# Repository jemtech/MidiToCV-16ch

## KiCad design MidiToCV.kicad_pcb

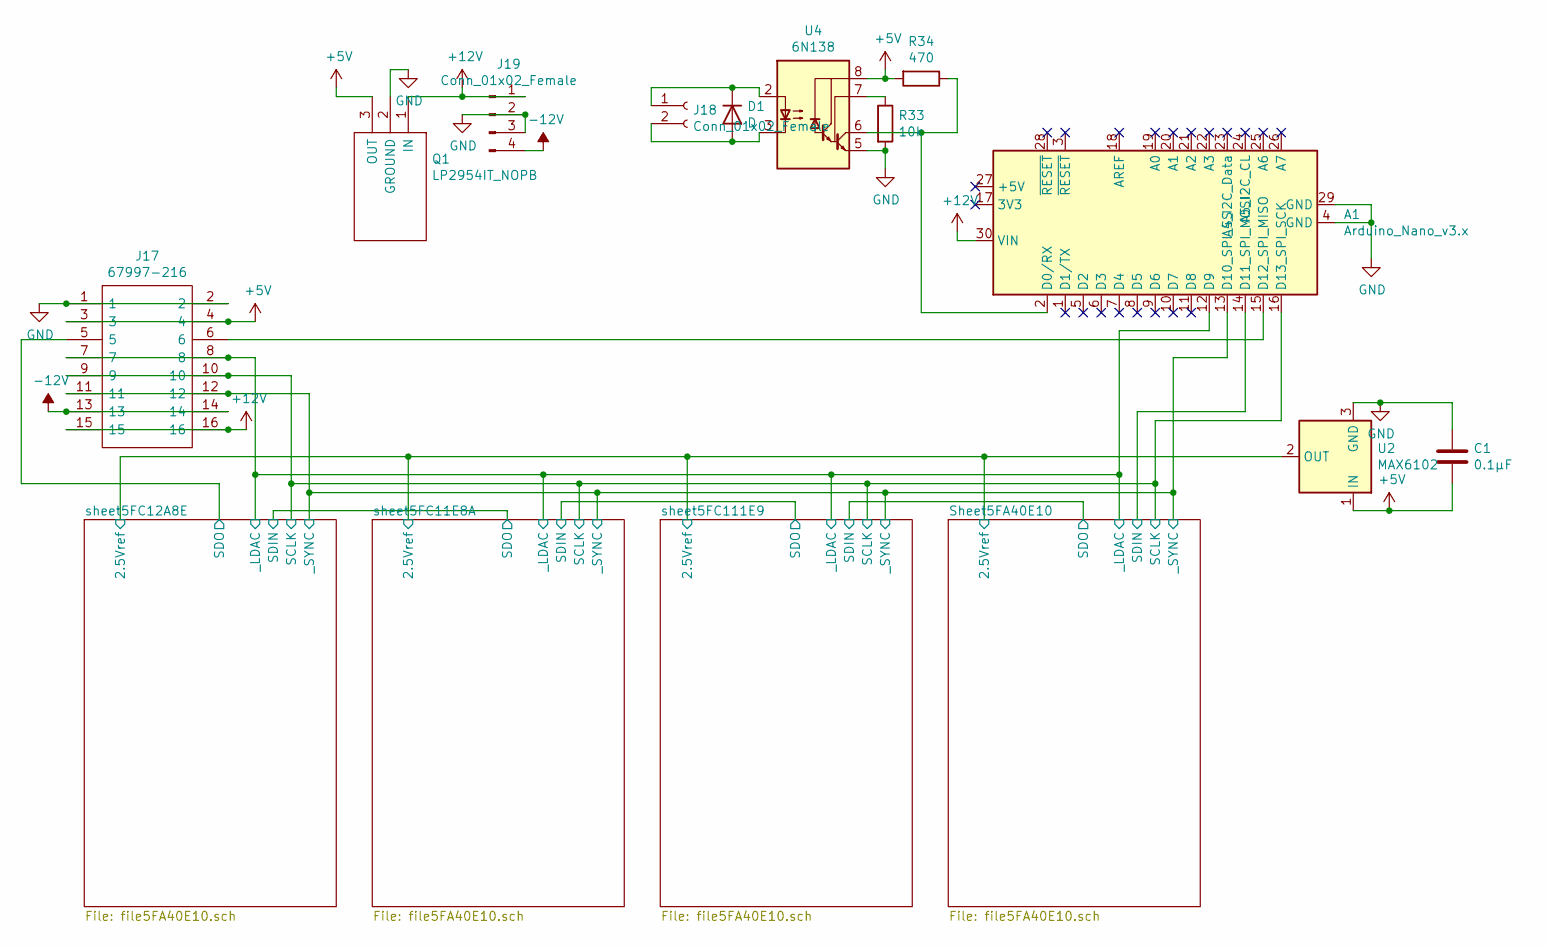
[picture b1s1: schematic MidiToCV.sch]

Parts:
A1: Arduino_Nano_v3.x; Arduino_Nano
C1: 0.1µF; C_0805_2012Metric_Pad1.15x1.40mm_HandSolder
D1: D; D_0805_2012Metric_Pad1.15x1.40mm_HandSolder
J17: 67997-216; HDRV16W90P254_2X8_2032X483X858P; Manufacturer_Part_Number 67997-216
J18: Conn_01x02_Female; PinHeader_1x02_P2.54mm_Vertical
J19: Conn_01x02_Female; PinHeader_1x04_P2.54mm_Vertical
Q1: LP2954IT_NOPB; TO254P470X1028X1955-3P; Mouser Part Number 926-LP2954IT/NOPB
R33: 10k; R_0805_2012Metric_Pad1.15x1.40mm_HandSolder
R34: 470; R_0805_2012Metric_Pad1.15x1.40mm_HandSolder
U2: MAX6102; SOT-23
U4: 6N138; SOP254P1016X460-8N

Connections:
+5V: C1.2, J17.3, J17.4, Q1.3 (OUT), R34.2, U2.1 (IN), U4.8 (VCC); also elsewhere on the board
+12V: A1.30 (VIN), J17.15, J17.16, J19.1, Q1.1 (IN); also elsewhere on the board
-12V: J17.13, J17.14, J19.4; also elsewhere on the board
/Sheet5FA40E10/2.5Vref: U2.2 (OUT); also elsewhere on the board
/Sheet5FA40E10/SCLK: A1.16 (D13_SPI_SCK), J17.9, J17.10; also elsewhere on the board
/Sheet5FA40E10/SDIN: A1.14 (D11_SPI_MOSI); also elsewhere on the board
/Sheet5FA40E10/_LDAC: A1.12 (D9), J17.7, J17.8; also elsewhere on the board
/Sheet5FA40E10/_SYNC: A1.13 (D10_SPI_SS), J17.11, J17.12; also elsewhere on the board
/sheet5FC12A8E/SDO: J17.5; also elsewhere on the board
GND: A1.4 (GND), A1.29 (GND), C1.1, J17.1, J17.2, J19.2, J19.3, Q1.2 (GROUND), R33.2, U2.3 (GND), U4.5 (GND); also elsewhere on the board
unnamed: A1.2 (D0/RX), R34.1, U4.6 (VO2)
unnamed: A1.15 (D12_SPI_MISO), J17.6
unnamed: D1.1 (K), J18.1, U4.2 (C1)
unnamed: D1.2 (A), J18.2, U4.3 (C2)
unnamed: R33.1, U4.7 (VO1)

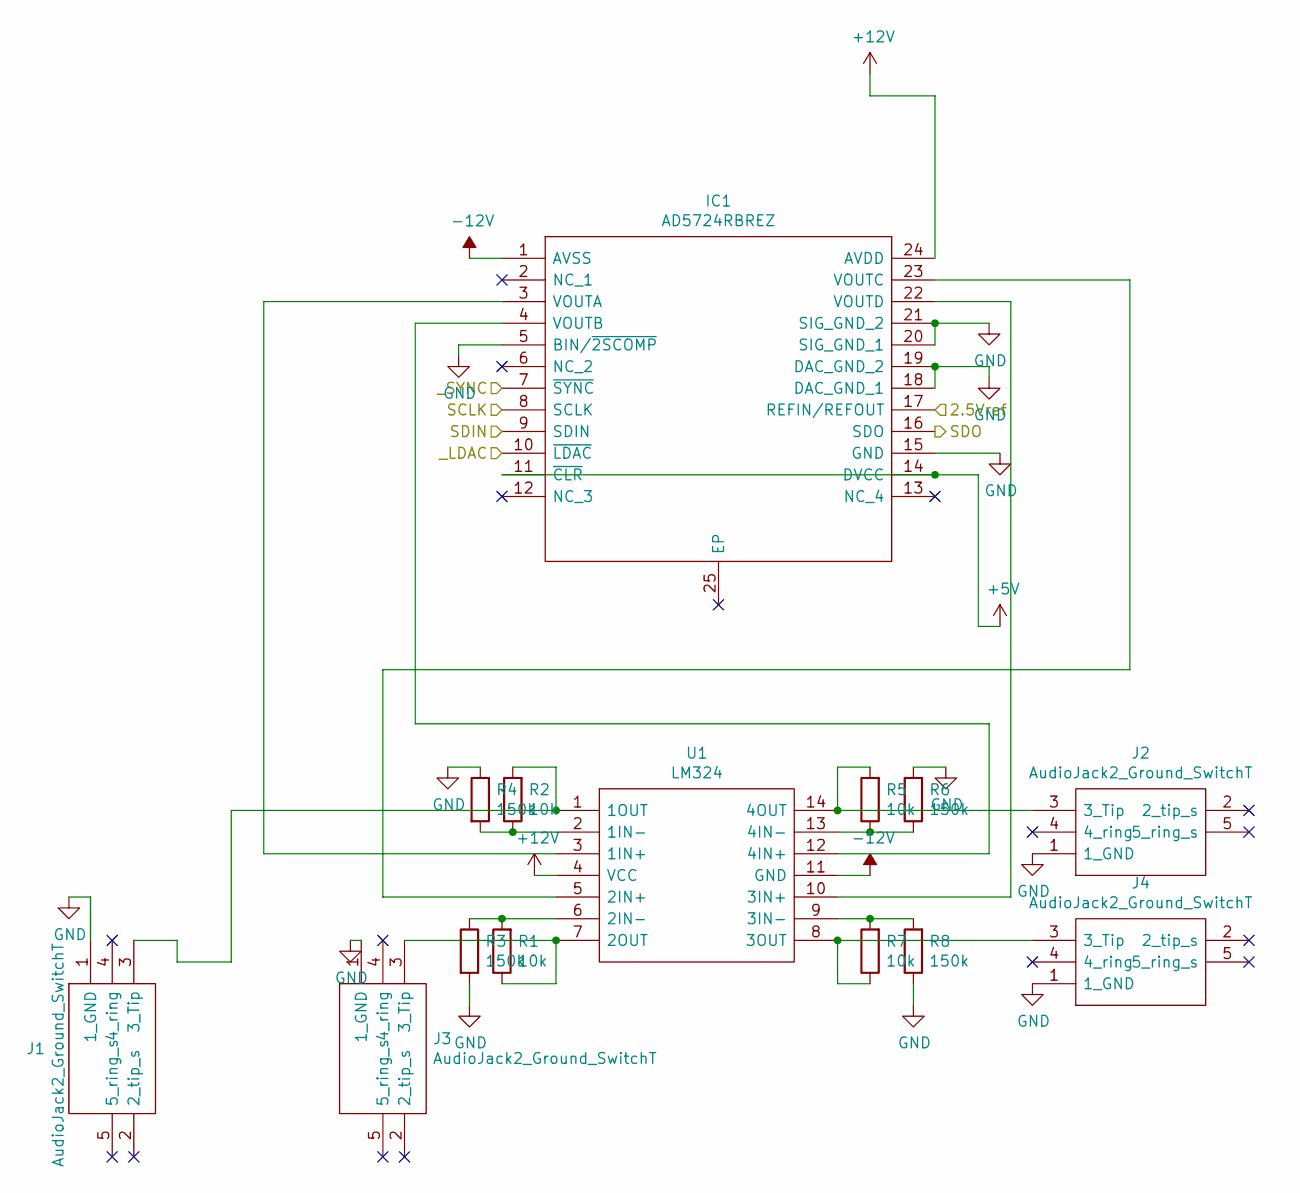
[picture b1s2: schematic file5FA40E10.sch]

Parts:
IC1: AD5724RBREZ; SOP65P640X120-25N; Mouser Part Number 584-AD5724RBREZ
J1, J2, J3, J4: AudioJack2_Ground_SwitchT; ACJS-NV35-XX; Manufacturer_Part_Number ACJS-NV35-5
R1, R2, R5, R7: 10k; R_0805_2012Metric_Pad1.15x1.40mm_HandSolder
R3, R4, R6, R8: 150k; R_0805_2012Metric_Pad1.15x1.40mm_HandSolder
U1: LM324; SOIC127P600X175-14N

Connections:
+5V: IC1.11 (~CLR), IC1.14 (DVCC); also elsewhere on the board
+12V: IC1.24 (AVDD), U1.4 (VCC); also elsewhere on the board
-12V: IC1.1 (AVSS), U1.11 (GND); also elsewhere on the board
/Sheet5FA40E10/2.5Vref: IC1.17 (REFIN/REFOUT); also elsewhere on the board
/Sheet5FA40E10/SCLK: IC1.8 (SCLK); also elsewhere on the board
/Sheet5FA40E10/SDIN: IC1.9 (SDIN); also elsewhere on the board
/Sheet5FA40E10/_LDAC: IC1.10 (~LDAC); also elsewhere on the board
/Sheet5FA40E10/_SYNC: IC1.7 (~SYNC); also elsewhere on the board
/sheet5FC111E9/SDIN: IC1.16 (SDO); also elsewhere on the board
GND: IC1.5 (BIN/~2SCOMP), IC1.15 (GND), IC1.18 (DAC_GND_1), IC1.19 (DAC_GND_2), IC1.20 (SIG_GND_1), IC1.21 (SIG_GND_2), J1.1 (1_GND), J2.1 (1_GND), J3.1 (1_GND), J4.1 (1_GND), R3.2, R4.1, R6.2, R8.1; also elsewhere on the board
unnamed: IC1.3 (VOUTA), U1.3 (1IN+)
unnamed: IC1.4 (VOUTB), U1.12 (4IN+)
unnamed: IC1.22 (VOUTD), U1.10 (3IN+)
unnamed: IC1.23 (VOUTC), U1.5 (2IN+)
unnamed: J1.3 (3_Tip), R2.2, U1.1 (1OUT)
unnamed: J2.3 (3_Tip), R5.2, U1.14 (4OUT)
unnamed: J3.3 (3_Tip), R1.1, U1.7 (2OUT)
unnamed: J4.3 (3_Tip), R7.1, U1.8 (3OUT)
unnamed: R1.2, R3.1, U1.6 (2IN-)
unnamed: R2.1, R4.2, U1.2 (1IN-)
unnamed: R5.1, R6.1, U1.13 (4IN-)
unnamed: R7.2, R8.2, U1.9 (3IN-)

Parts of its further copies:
IC2, IC3, IC4: AD5724RBREZ; SOP65P640X120-25N; Mouser Part Number 584-AD5724RBREZ
J5, J6, J7, J8, J9, J10, J11, J12, J13, J14, J15, J16: AudioJack2_Ground_SwitchT; ACJS-NV35-XX; Manufacturer_Part_Number ACJS-NV35-5
R9, R10, R15, R16, R17, R18, R23, R24, R25, R26, R31, R32: 150k; R_0805_2012Metric_Pad1.15x1.40mm_HandSolder
R11, R12, R13, R14, R19, R20, R21, R22, R27, R28, R29, R30: 10k; R_0805_2012Metric_Pad1.15x1.40mm_HandSolder
U3, U5, U7: LM324; SOIC127P600X175-14N

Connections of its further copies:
+5V: IC2.11 (~CLR), IC2.14 (DVCC), IC3.11 (~CLR), IC3.14 (DVCC), IC4.11 (~CLR), IC4.14 (DVCC); also elsewhere on the board
+12V: IC2.24 (AVDD), IC3.24 (AVDD), IC4.24 (AVDD), U3.4 (VCC), U5.4 (VCC), U7.4 (VCC); also elsewhere on the board
-12V: IC2.1 (AVSS), IC3.1 (AVSS), IC4.1 (AVSS), U3.11 (GND), U5.11 (GND), U7.11 (GND); also elsewhere on the board
/Sheet5FA40E10/2.5Vref: IC2.17 (REFIN/REFOUT), IC3.17 (REFIN/REFOUT), IC4.17 (REFIN/REFOUT); also elsewhere on the board
/Sheet5FA40E10/SCLK: IC2.8 (SCLK), IC3.8 (SCLK), IC4.8 (SCLK); also elsewhere on the board
/Sheet5FA40E10/_LDAC: IC2.10 (~LDAC), IC3.10 (~LDAC), IC4.10 (~LDAC); also elsewhere on the board
/Sheet5FA40E10/_SYNC: IC2.7 (~SYNC), IC3.7 (~SYNC), IC4.7 (~SYNC); also elsewhere on the board
/sheet5FC11E8A/SDIN: IC2.16 (SDO), IC3.9 (SDIN)
/sheet5FC12A8E/SDIN: IC3.16 (SDO), IC4.9 (SDIN)
/sheet5FC12A8E/SDO: IC4.16 (SDO); also elsewhere on the board
/sheet5FC111E9/SDIN: IC2.9 (SDIN); also elsewhere on the board
GND: IC2.5 (BIN/~2SCOMP), IC2.15 (GND), IC2.18 (DAC_GND_1), IC2.19 (DAC_GND_2), IC2.20 (SIG_GND_1), IC2.21 (SIG_GND_2), IC3.5 (BIN/~2SCOMP), IC3.15 (GND), IC3.18 (DAC_GND_1), IC3.19 (DAC_GND_2), IC3.20 (SIG_GND_1), IC3.21 (SIG_GND_2), IC4.5 (BIN/~2SCOMP), IC4.15 (GND), IC4.18 (DAC_GND_1), IC4.19 (DAC_GND_2), IC4.20 (SIG_GND_1), IC4.21 (SIG_GND_2), J5.1 (1_GND), J6.1 (1_GND), J7.1 (1_GND), J8.1 (1_GND), J9.1 (1_GND), J10.1 (1_GND), J11.1 (1_GND), J12.1 (1_GND), J13.1 (1_GND), J14.1 (1_GND), J15.1 (1_GND), J16.1 (1_GND), R9.2, R10.1, R15.2, R16.1, R17.2, R18.1, R23.2, R24.1, R25.2, R26.1, R31.2, R32.1; also elsewhere on the board
unnamed: IC2.3 (VOUTA), U3.3 (1IN+)
unnamed: IC2.4 (VOUTB), U3.12 (4IN+)
unnamed: IC2.22 (VOUTD), U3.10 (3IN+)
unnamed: IC2.23 (VOUTC), U3.5 (2IN+)
unnamed: IC3.3 (VOUTA), U5.3 (1IN+)
unnamed: IC3.4 (VOUTB), U5.12 (4IN+)
unnamed: IC3.22 (VOUTD), U5.10 (3IN+)
unnamed: IC3.23 (VOUTC), U5.5 (2IN+)
unnamed: IC4.3 (VOUTA), U7.3 (1IN+)
unnamed: IC4.4 (VOUTB), U7.12 (4IN+)
unnamed: IC4.22 (VOUTD), U7.10 (3IN+)
unnamed: IC4.23 (VOUTC), U7.5 (2IN+)
unnamed: J5.3 (3_Tip), R12.2, U3.1 (1OUT)
unnamed: J6.3 (3_Tip), R13.2, U3.14 (4OUT)
unnamed: J7.3 (3_Tip), R11.1, U3.7 (2OUT)
unnamed: J8.3 (3_Tip), R14.1, U3.8 (3OUT)
unnamed: J9.3 (3_Tip), R20.2, U5.1 (1OUT)
unnamed: J10.3 (3_Tip), R21.2, U5.14 (4OUT)
unnamed: J11.3 (3_Tip), R19.1, U5.7 (2OUT)
unnamed: J12.3 (3_Tip), R22.1, U5.8 (3OUT)
unnamed: J13.3 (3_Tip), R28.2, U7.1 (1OUT)
unnamed: J14.3 (3_Tip), R29.2, U7.14 (4OUT)
unnamed: J15.3 (3_Tip), R27.1, U7.7 (2OUT)
unnamed: J16.3 (3_Tip), R30.1, U7.8 (3OUT)
unnamed: R10.2, R12.1, U3.2 (1IN-)
unnamed: R9.1, R11.2, U3.6 (2IN-)
unnamed: R13.1, R15.1, U3.13 (4IN-)
unnamed: R14.2, R16.2, U3.9 (3IN-)
unnamed: R17.1, R19.2, U5.6 (2IN-)
unnamed: R18.2, R20.1, U5.2 (1IN-)
unnamed: R21.1, R23.1, U5.13 (4IN-)
unnamed: R22.2, R24.2, U5.9 (3IN-)
unnamed: R25.1, R27.2, U7.6 (2IN-)
unnamed: R26.2, R28.1, U7.2 (1IN-)
unnamed: R29.1, R31.1, U7.13 (4IN-)
unnamed: R30.2, R32.2, U7.9 (3IN-)

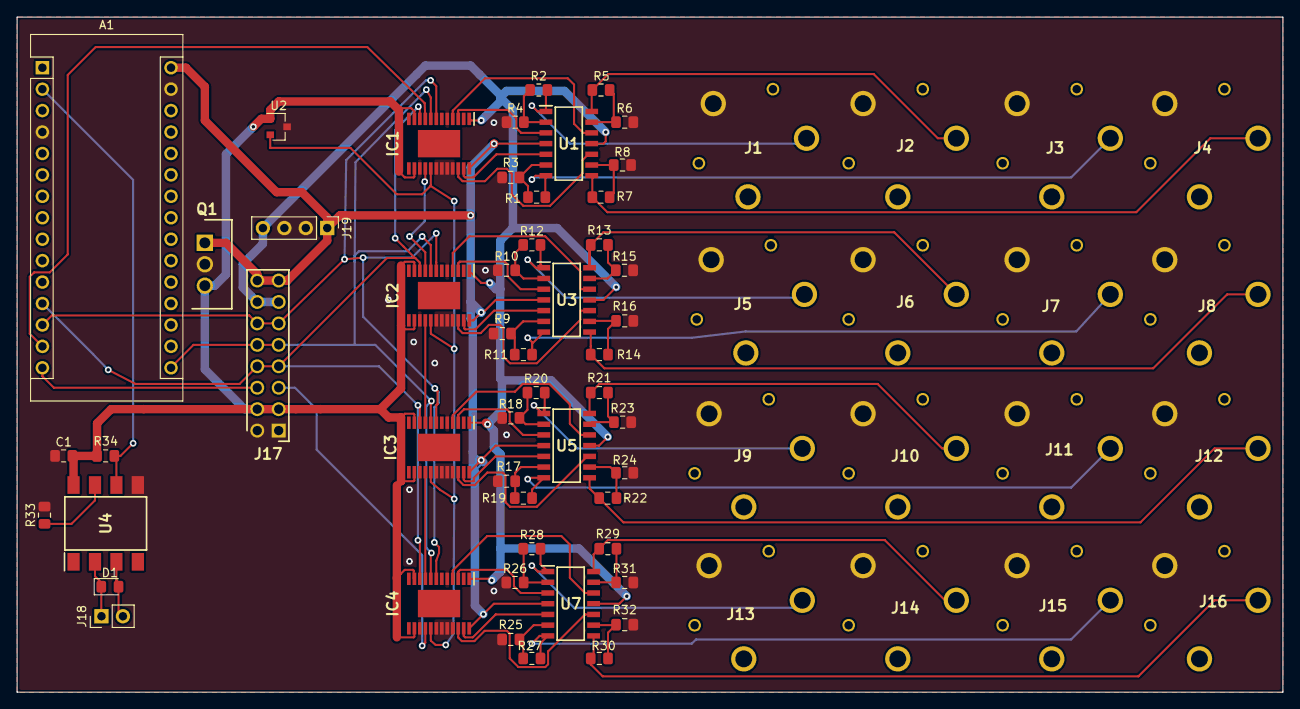
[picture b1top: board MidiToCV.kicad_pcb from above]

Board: 2 copper layers, 150.0 x 80.0 mm, 67 parts (0 on the bottom side), 66 nets.

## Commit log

2021-02-27 ladc_ bug fix
2021-02-27 clean old files
